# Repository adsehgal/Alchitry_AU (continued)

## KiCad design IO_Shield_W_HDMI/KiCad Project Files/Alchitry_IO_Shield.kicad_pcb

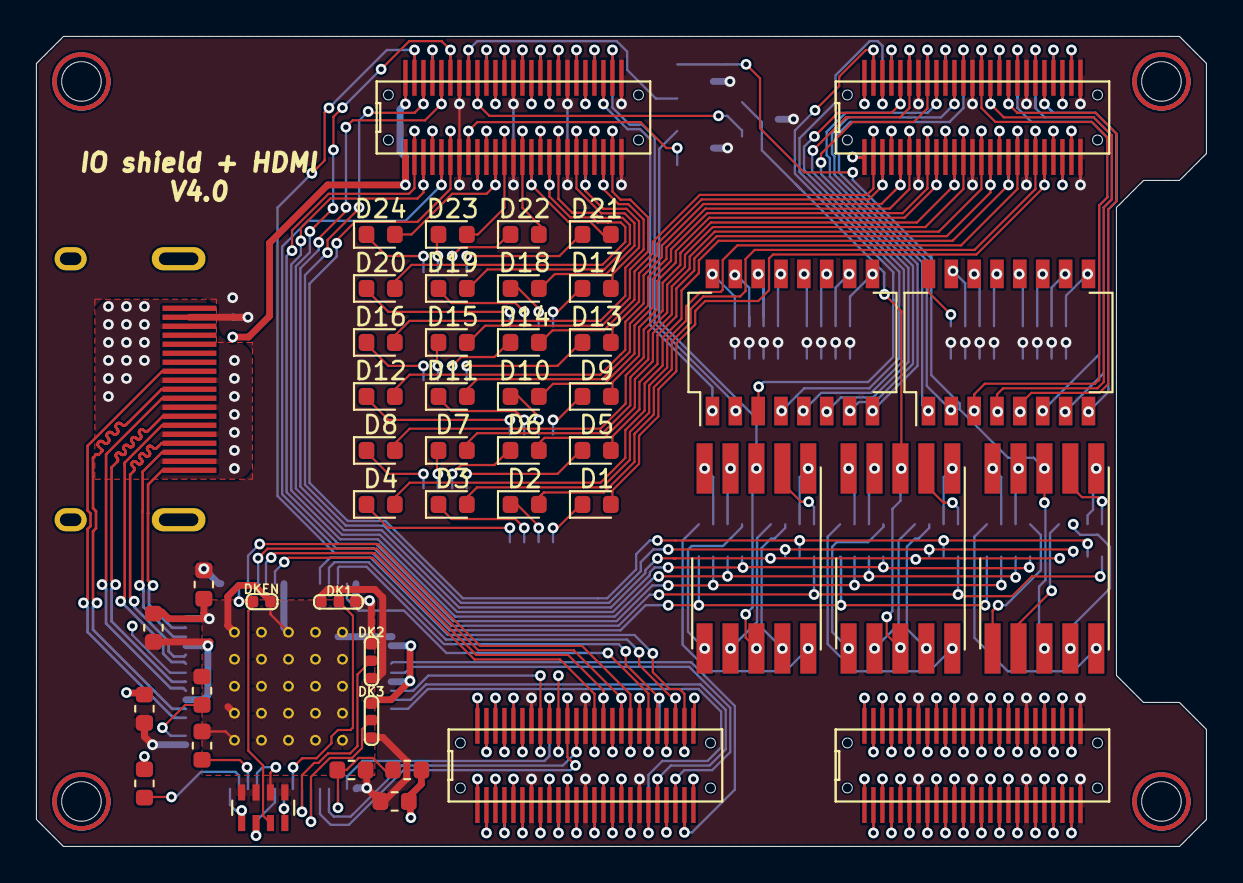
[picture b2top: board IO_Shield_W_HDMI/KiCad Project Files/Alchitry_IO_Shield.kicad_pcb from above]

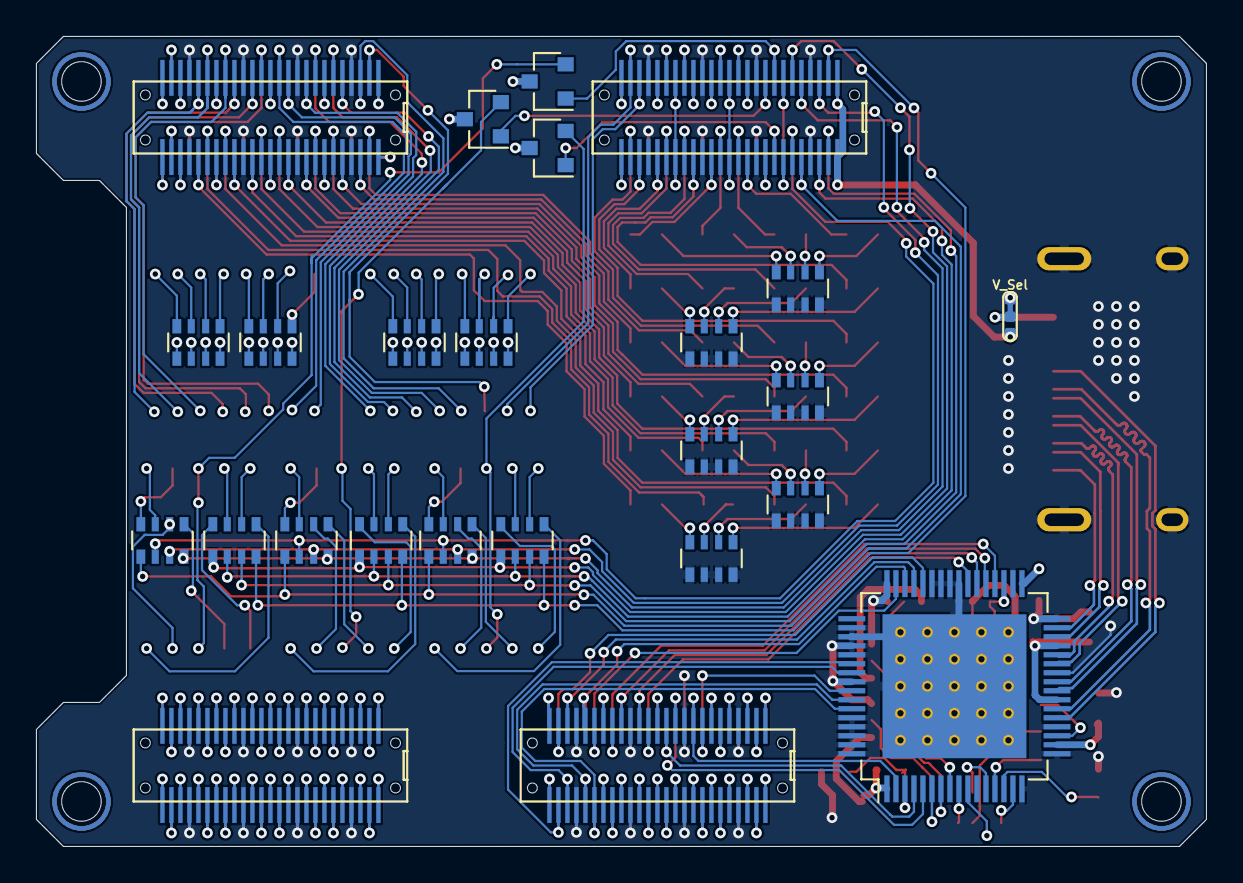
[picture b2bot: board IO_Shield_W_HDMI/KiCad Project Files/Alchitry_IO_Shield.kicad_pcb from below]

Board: 4 copper layers, 65.0 x 45.0 mm, 66 parts (21 on the bottom side), 226 nets.

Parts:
AFF1, AFF2, AFF3: LTS-6960HR; KCSC02-136
C1, C2, C3, C4: 100nF; C_0603_1608Metric
D1, D2, D3, D4, D5, D6, D7, D8, D9, D10, D11, D12, D13, D14, D15, D16, D17, D18, D19, D20, D21, D22, D23, D24: LED; LED_0603_1608Metric
J1: HDMI_A_1.4; HDMI
JP1: V_Sel; jumper_1_2_bridged
JP2: DK1; jumper_unbridged
JP3: DK2; jumper_unbridged
JP4: DK3; jumper_unbridged
JP5: DKEN; Jumper_2_Pin_Unbridged
Q1, Q2, Q3: Q_PMOS_SGD; SOT-23
R1: 510; R_0603_1608Metric
R2, R3: 10K; R_0603_1608Metric
R4: 33K; R_0603_1608Metric
R5: 91K; R_0603_1608Metric
RN1: 10K; R_Array_Concave_4x0603
RN2, RN3, RN4, RN5, RN6, RN7, RN8, RN9, RN10, RN11, RN12, RN13, RN14, RN15, RN16, RN17: R_Pack04; R_Array_Convex_4x0603
SW1, SW2: SW_DIP_x08; SW_DIP_SPSTx08_Slide_Copal_CHS-08B_W7.62mm_P1.27mm
U1: boardmezzanine_new; Alchitry_Top_Bottom
U2: TFP410; HTQFP-64-1EP_10x10mm_P0.5mm_EP8x8mm_Mask4.4x4.4mm_ThermalVi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

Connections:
+3V3: C1.1, C2.1, C3.1, C4.1, J1.18 (+5V), JP1.1 (A), JP1.2 (C), JP2.1 (A), JP3.1 (A), JP4.1 (A), Q1.3 (D), Q2.3 (D), Q3.3 (D), R1.1, R4.2, RN1.1 (R1.1), RN1.2 (R2.1), RN1.3 (R3.1), RN1.4 (R4.1), RN14.1 (R1.1), RN14.2 (R2.1), RN14.3 (R3.1), RN14.4 (R4.1), RN15.1 (R1.1), RN15.2 (R2.1), RN15.3 (R3.1), RN15.4 (R4.1), RN16.1 (R1.1), RN16.2 (R2.1), RN16.3 (R3.1), RN16.4 (R4.1), RN17.1 (R1.1), RN17.2 (R2.1), RN17.3 (R3.1), RN17.4 (R4.1), U1.AB_7, U1.AB_13, U1.AB_19, U1.AB_25, U1.AB_26, U1.AB_32, U1.AB_38, U1.AB_44, U1.AT_7 (3.3V), U1.AT_13 (3.3V), U1.AT_19 (3.3V), U1.AT_25 (3.3V), U1.AT_26 (3.3V), U1.AT_32 (3.3V), U1.AT_38 (3.3V), U1.AT_44 (3.3V), U1.BB_7, U1.BB_13, U1.BB_19, U1.BB_25, U1.BB_26, U1.BB_32, U1.BB_38, U1.BB_44, U1.BT_7 (3.3V), U1.BT_13 (3.3V), U1.BT_19 (3.3V), U1.BT_25 (3.3V), U1.BT_26 (3.3V), U1.BT_32 (3.3V), U1.BT_38 (3.3V), U1.BT_44 (3.3V), U1.CB_7, U1.CB_13, U1.CB_19, U1.CB_38, U1.CB_44, U1.CT_7 (3.3V), U1.CT_13 (3.3V), U1.CT_19 (3.3V), U1.CT_38 (3.3V), U1.CT_44 (3.3V), U1.DB_7, U1.DB_13, U1.DB_19, U1.DB_25, U1.DB_26, U1.DB_32, U1.DB_38, U1.DB_44, U1.DT_7 (3.3V), U1.DT_13 (3.3V), U1.DT_19 (3.3V), U1.DT_25 (3.3V), U1.DT_26 (3.3V), U1.DT_32 (3.3V), U1.DT_38 (3.3V), U1.DT_44 (3.3V), U2.1 (DVDD_2), U2.12 (DVDD_3), U2.18 (PVDD), U2.23 (TVDD_2), U2.29 (TVDD), U2.33 (DVDD)
+5V: JP1.3 (B), U1.AB_1, U1.AB_50, U1.AT_1 (Raw), U1.AT_50 (Raw)
/AN0: Q1.1 (G), U1.AB_43, U1.AT_43 (P9)
/AN1: Q2.1 (G), U1.AB_42, U1.AT_42 (N9)
/AN2: Q3.1 (G), U1.AB_8, U1.AT_8 (R8)
/AN3: U1.AB_9, U1.AT_9 (P8)
/B0: U1.CB_20, U1.CT_20 (N4), U2.59 (DATA4)
/B1: U1.CB_21, U1.CT_21 (M5), U2.58 (DATA5)
/B2: U1.CB_23, U1.CT_23 (L5), U2.55 (DATA6)
/B3: U1.CB_24, U1.CT_24 (P5), U2.54 (DATA7)
/BTN0: U1.BB_28, U1.BT_28 (C6)
/BTN1: U1.BB_27, U1.BT_27 (C7)
/BTN2: U1.BB_23, U1.BT_23 (A7)
/BTN3: U1.BB_24, U1.BT_24 (B7)
/BTN4: U1.CB_49, U1.CT_49 (P11)
/BTN5: U1.CB_48, U1.CT_48 (P10)
/BTN6: U1.CB_46, U1.CT_46 (N12)
/C0: RN5.1 (R1.1), RN6.1 (R1.1), RN12.1 (R1.1), U1.AB_5, U1.AT_5 (T5)
/C1: RN5.2 (R2.1), RN6.2 (R2.1), RN12.2 (R2.1), U1.AB_6, U1.AT_6 (R5)
/C2: RN5.3 (R3.1), RN6.3 (R3.1), RN12.3 (R3.1), U1.AB_48, U1.AT_48 (T9)
/C3: RN5.4 (R4.1), RN6.4 (R4.1), RN12.4 (R4.1), U1.AB_46, U1.AT_46 (R6)
/C4: RN7.1 (R1.1), RN8.1 (R1.1), RN13.1 (R1.1), U1.AB_45, U1.AT_45 (R7)
/C5: RN7.2 (R2.1), RN8.2 (R2.1), RN13.2 (R2.1), U1.AB_3, U1.AT_3 (T7)
/C6: RN7.3 (R3.1), RN8.3 (R3.1), RN13.3 (R3.1), U1.AB_2, U1.AT_2 (T8)
/CLK: U1.CB_43, U1.CT_43 (P13), U2.57 (IDCK+)
/DE: U1.CB_42, U1.CT_42 (N13), U2.2 (DE)
/DIP0: SW1.8, U1.BB_30, U1.BT_30 (D6)
/DIP1: SW1.7, U1.BB_31, U1.BT_31 (D5)
/DIP2: SW1.6, U1.BB_33, U1.BT_33 (F5)
/DIP3: SW1.5, U1.BB_34, U1.BT_34 (E5)
/DIP4: SW1.4, U1.BB_36, U1.BT_36 (G5)
/DIP5: SW1.3, U1.BB_37, U1.BT_37 (G4)
/DIP6: SW1.2, U1.BB_39, U1.BT_39 (D4)
/DIP7: SW1.1, U1.BB_40, U1.BT_40 (C4)
/DIP8: SW2.8, U1.BB_42, U1.BT_42 (E3)
/DIP9: SW2.7, U1.BB_43, U1.BT_43 (D3)
/DIP10: SW2.6, U1.BB_45, U1.BT_45 (C3)
/DIP11: SW2.5, U1.BB_46, U1.BT_46 (C2)
/DIP12: SW2.4, U1.BB_48, U1.BT_48 (C1)
/DIP13: SW2.3, U1.BB_49, U1.BT_49 (B1)
/DIP14: SW2.2, U1.AB_27, U1.AT_27 (M6)
/DIP15: SW2.1, U1.AB_28, U1.AT_28 (N6)
/DIP16: U1.AB_30, U1.AT_30 (H5)
/DIP17: U1.AB_31, U1.AT_31 (H4)
/DIP18: U1.AB_33, U1.AT_33 (J3)
/DIP19: U1.AB_34, U1.AT_34 (H3)
/DIP20: U1.AB_36, U1.AT_36 (J5)
/DIP21: U1.AB_37, U1.AT_37 (J4)
/DIP22: U1.AB_39, U1.AT_39 (K3)
/DIP23: U1.AB_40, U1.AT_40 (K2)
/DP: RN7.4 (R4.1), RN8.4 (R4.1), RN13.4 (R4.1), U1.AB_49, U1.AT_49 (T10)
/G0: U1.CB_31, U1.CT_31 (T2), U2.47 (DATA12)
/G1: U1.CB_30, U1.CT_30 (R3), U2.46 (DATA13)
/G2: U1.CB_28, U1.CT_28 (T3), U2.45 (DATA14)
/G3: U1.CB_27, U1.CT_27 (T4), U2.44 (DATA15)
/HDMI/CK+: J1.10 (CK+), U2.22 (TXC+)
/HDMI/CK-: J1.12 (CK-), U2.21 (TXC-)
/HDMI/D0+: J1.7 (D0+), U2.25 (TX0+)
/HDMI/D0-: J1.9 (D0-), U2.24 (TX0-)
/HDMI/D1+: J1.4 (D1+), U2.28 (TX1+)
/HDMI/D1-: J1.6 (D1-), U2.27 (TX1-)
/HDMI/D2+: J1.1 (D2+), U2.31 (TX2+)
/HDMI/D2-: J1.3 (D2-), U2.30 (TX2-)
/HDMI/DK1: JP2.2 (C), U2.8 (CTL1/A1/DK1)
/HDMI/DK2: JP3.2 (C), U2.7 (CTL2/A2/DK2)
/HDMI/DK3: JP4.2 (C), U2.6 (CTL3/A3/DK3)
/HDMI/ISEL: R2.1, U2.13 (ISEL/~RST)
/HS: U1.CB_39, U1.CT_39 (M2), U2.4 (HSYNC)
/LED0: D1.2 (A), U1.BB_21, U1.BT_21 (B6)
/LED1: D2.2 (A), U1.BB_20, U1.BT_20 (B5)
/LED2: D3.2 (A), U1.BB_18, U1.BT_18 (A5)
/LED3: D4.2 (A), U1.BB_17, U1.BT_17 (A4)
/LED4: D5.2 (A), U1.BB_15, U1.BT_15 (B4)
/LED5: D6.2 (A), U1.BB_14, U1.BT_14 (A3)
/LED6: D7.2 (A), U1.BB_12, U1.BT_12 (F4)
/LED7: D8.2 (A), U1.BB_11, U1.BT_11 (F3)
/LED8: D9.2 (A), U1.BB_9, U1.BT_9 (F2)
/LED9: D10.2 (A), U1.BB_8, U1.BT_8 (E1)
/LED10: D11.2 (A), U1.BB_6, U1.BT_6 (B2)
/LED11: D12.2 (A), U1.BB_5, U1.BT_5 (A2)
/LED12: D13.2 (A), U1.BB_3, U1.BT_3 (E2)
/LED13: D14.2 (A), U1.BB_2, U1.BT_2 (D1)
/LED14: D15.2 (A), U1.AB_24, U1.AT_24 (E6)
/LED15: D16.2 (A), U1.AB_23, U1.AT_23 (K5)
/LED16: D17.2 (A), U1.AB_21, U1.AT_21 (G2)
/LED17: D18.2 (A), U1.AB_20, U1.AT_20 (G1)
/LED18: D19.2 (A), U1.AB_18, U1.AT_18 (H2)
/LED19: D20.2 (A), U1.AB_17, U1.AT_17 (H1)
/LED20: D21.2 (A), U1.AB_15, U1.AT_15 (K1)
/LED21: D22.2 (A), U1.AB_14, U1.AT_14 (J1)
/LED22: D23.2 (A), U1.AB_12, U1.AT_12 (L3)
/LED23: D24.2 (A), U1.AB_11, U1.AT_11 (L2)
/R0: U1.CB_37, U1.CT_37 (P1), U2.39 (DATA20)
/R1: U1.CB_36, U1.CT_36 (N1), U2.38 (DATA21)
/R2: U1.CB_34, U1.CT_34 (R1), U2.37 (DATA22)
/R3: U1.CB_33, U1.CT_33 (R2), U2.36 (DATA23)
/VS: U1.CB_40, U1.CT_40 (M1), U2.5 (VSYNC)
GNDREF: C1.2, C2.2, C3.2, C4.2, J1.2 (D2S), J1.5 (D1S), J1.8 (D0S), J1.11 (CKS), J1.17 (GND), J1.SH, JP2.3 (B), JP3.3 (B), JP4.3 (B), JP5.1 (A), R2.2, R3.2, R5.2, RN2.1 (R1.1), RN2.2 (R2.1), RN2.3 (R3.1), RN2.4 (R4.1), RN3.1 (R1.1), RN3.2 (R2.1), RN3.3 (R3.1), RN3.4 (R4.1), RN4.1 (R1.1), RN4.2 (R2.1), RN4.3 (R3.1), RN4.4 (R4.1), RN9.1 (R1.1), RN9.2 (R2.1), RN9.3 (R3.1), RN9.4 (R4.1), RN10.1 (R1.1), RN10.2 (R2.1), RN10.3 (R3.1), RN10.4 (R4.1), RN11.1 (R1.1), RN11.2 (R2.1), RN11.3 (R3.1), RN11.4 (R4.1), U1.AB_4, U1.AB_10, U1.AB_16, U1.AB_22, U1.AB_29, U1.AB_35, U1.AB_41, U1.AB_47, U1.AT_4 (GND), U1.AT_10 (GND), U1.AT_16 (GND), U1.AT_22 (GND), U1.AT_29 (GND), U1.AT_35 (GND), U1.AT_41 (GND), U1.AT_47 (GND), U1.BB_4, U1.BB_10, U1.BB_16, U1.BB_22, U1.BB_29, U1.BB_35, U1.BB_41, U1.BB_47, U1.BT_4 (GND), U1.BT_10 (GND), U1.BT_16 (GND), U1.BT_22 (GND), U1.BT_29 (GND), U1.BT_35 (GND), U1.BT_41 (GND), U1.BT_47 (GND), U1.CB_4, U1.CB_10, U1.CB_16, U1.CB_22, U1.CB_29, U1.CB_35, U1.CB_41, U1.CB_47, U1.CT_4 (GND), U1.CT_10 (GND), U1.CT_16 (GND), U1.CT_22 (GND), U1.CT_29 (GND), U1.CT_35 (GND), U1.CT_41 (GND), U1.CT_47 (GND), U1.DB_4, U1.DB_10, U1.DB_16, U1.DB_22, U1.DB_29, U1.DB_35, U1.DB_41, U1.DB_47, U1.DT_4 (GND), U1.DT_10 (GND), U1.DT_16 (GND), U1.DT_22 (GND), U1.DT_29 (GND), U1.DT_35 (GND), U1.DT_41 (GND), U1.DT_47 (GND), U2.16 (DGND_3), U2.17 (PGND), U2.20 (TGND_2), U2.26 (TGND_3), U2.32 (TGND), U2.34 (RESERVED), U2.40 (DATA19), U2.41 (DATA18), U2.42 (DATA17), U2.43 (DATA16), U2.48 (DGND_2), U2.50 (DATA11), U2.51 (DATA10), U2.52 (DATA9), U2.53 (DATA8), U2.56 (IDCK-), U2.60 (DATA3), U2.61 (DATA2), U2.62 (DATA1), U2.63 (DATA0), U2.64 (DGND), U2.65 (PAD)
unnamed: AFF1.1 (e), RN7.8 (R1.2)
unnamed: AFF1.2 (d), RN5.5 (R4.2)
unnamed: AFF1.3 (C.A.), AFF1.8 (C.A.), Q1.2 (S)
unnamed: AFF1.4 (c), RN5.6 (R3.2)
unnamed: AFF1.5 (DP), RN7.5 (R4.2)
unnamed: AFF1.6 (b), RN5.7 (R2.2)
unnamed: AFF1.7 (a), RN5.8 (R1.2)
unnamed: AFF1.9 (f), RN7.7 (R2.2)
unnamed: AFF1.10 (g), RN7.6 (R3.2)
unnamed: AFF2.1 (e), RN8.8 (R1.2)
unnamed: AFF2.2 (d), RN6.5 (R4.2)
unnamed: AFF2.3 (C.A.), AFF2.8 (C.A.), Q2.2 (S)
unnamed: AFF2.4 (c), RN6.6 (R3.2)
unnamed: AFF2.5 (DP), RN8.5 (R4.2)
unnamed: AFF2.6 (b), RN6.7 (R2.2)
unnamed: AFF2.7 (a), RN6.8 (R1.2)
unnamed: AFF2.9 (f), RN8.7 (R2.2)
unnamed: AFF2.10 (g), RN8.6 (R3.2)
unnamed: AFF3.1 (e), RN13.8 (R1.2)
unnamed: AFF3.2 (d), RN12.5 (R4.2)
unnamed: AFF3.3 (C.A.), AFF3.8 (C.A.), Q3.2 (S)
unnamed: AFF3.4 (c), RN12.6 (R3.2)
unnamed: AFF3.5 (DP), RN13.5 (R4.2)
unnamed: AFF3.6 (b), RN12.7 (R2.2)
unnamed: AFF3.7 (a), RN12.8 (R1.2)
unnamed: AFF3.9 (f), RN13.7 (R2.2)
unnamed: AFF3.10 (g), RN13.6 (R3.2)
unnamed: D1.1 (K), RN2.8 (R1.2)
unnamed: D2.1 (K), RN2.7 (R2.2)
unnamed: D3.1 (K), RN2.6 (R3.2)
unnamed: D4.1 (K), RN2.5 (R4.2)
unnamed: D5.1 (K), RN3.8 (R1.2)
unnamed: D6.1 (K), RN3.7 (R2.2)
unnamed: D7.1 (K), RN3.6 (R3.2)
unnamed: D8.1 (K), RN3.5 (R4.2)
unnamed: D9.1 (K), RN4.8 (R1.2)
unnamed: D10.1 (K), RN4.7 (R2.2)
unnamed: D11.1 (K), RN4.6 (R3.2)
unnamed: D12.1 (K), RN4.5 (R4.2)
unnamed: D13.1 (K), RN9.8 (R1.2)
unnamed: D14.1 (K), RN9.7 (R2.2)
unnamed: D15.1 (K), RN9.6 (R3.2)
unnamed: D16.1 (K), RN9.5 (R4.2)
unnamed: D17.1 (K), RN10.8 (R1.2)
unnamed: D18.1 (K), RN10.7 (R2.2)
unnamed: D19.1 (K), RN10.6 (R3.2)
unnamed: D20.1 (K), RN10.5 (R4.2)
unnamed: D21.1 (K), RN11.8 (R1.2)
unnamed: D22.1 (K), RN11.7 (R2.2)
unnamed: D23.1 (K), RN11.6 (R3.2)
unnamed: D24.1 (K), RN11.5 (R4.2)
unnamed: JP5.2 (B), RN1.7 (R2.2), U2.35 (DKEN)
unnamed: R1.2, U2.19 (TFADJ)
unnamed: R3.1, U2.14 (DSEL/SDA)
unnamed: R4.1, R5.1, U2.3 (VREF)
unnamed: RN1.5 (R4.2), U2.15 (BSEL/SCL)
unnamed: RN1.6 (R3.2), U2.10 (~PD)
unnamed: RN1.8 (R1.2), U2.9 (EDGE/HTPLG)
unnamed: RN14.5 (R4.2), SW1.12
unnamed: RN14.6 (R3.2), SW1.11
unnamed: RN14.7 (R2.2), SW1.10
unnamed: RN14.8 (R1.2), SW1.9
unnamed: RN15.5 (R4.2), SW1.16
unnamed: RN15.6 (R3.2), SW1.15
unnamed: RN15.7 (R2.2), SW1.14
unnamed: RN15.8 (R1.2), SW1.13
unnamed: RN16.5 (R4.2), SW2.12
unnamed: RN16.6 (R3.2), SW2.11
unnamed: RN16.7 (R2.2), SW2.10
unnamed: RN16.8 (R1.2), SW2.9
unnamed: RN17.5 (R4.2), SW2.16
unnamed: RN17.6 (R3.2), SW2.15
unnamed: RN17.7 (R2.2), SW2.14
unnamed: RN17.8 (R1.2), SW2.13
unnamed: U1.BB_1, U1.BT_1 (Raw)
unnamed: U1.BB_50, U1.BT_50 (Raw)
unnamed: U1.CB_1, U1.CT_1 (Raw)
unnamed: U1.CB_2, U1.CT_2 (T13)
unnamed: U1.CB_3, U1.CT_3 (R13)
unnamed: U1.CB_5, U1.CT_5 (T12)
unnamed: U1.CB_6, U1.CT_6 (R12)
unnamed: U1.CB_8, U1.CT_8 (R11)
unnamed: U1.CB_9, U1.CT_9 (R10)
unnamed: U1.CB_11, U1.CT_11 (N2)
unnamed: U1.CB_12, U1.CT_12 (N3)
unnamed: U1.CB_14, U1.CT_14 (P3)
unnamed: U1.CB_15, U1.CT_15 (P4)
unnamed: U1.CB_17, U1.CT_17 (M4)
unnamed: U1.CB_18, U1.CT_18 (L4)
unnamed: U1.CB_25, U1.CT_25 (3.3V)
unnamed: U1.CB_26, U1.CT_26 (3.3V)
unnamed: U1.CB_32, U1.CT_32 (3.3V)
unnamed: U1.CB_45, U1.CT_45 (N11)
unnamed: U1.CB_50, U1.CT_50 (Raw)
unnamed: U1.DB_1, U1.DT_1 (Raw)
unnamed: U1.DB_2, U1.DT_2 (LED2)
unnamed: U1.DB_3, U1.DT_3 (LED3)
unnamed: U1.DB_5, U1.DT_5 (LED6)
unnamed: U1.DB_6, U1.DT_6 (LED7)
unnamed: U1.DB_8, U1.DT_8 (R16)
unnamed: U1.DB_9, U1.DT_9 (R15)
unnamed: U1.DB_11, U1.DT_11 (P14)
unnamed: U1.DB_12, U1.DT_12 (M15)
unnamed: U1.DB_14, U1.DT_14 (TX)
unnamed: U1.DB_15, U1.DT_15 (RX)
unnamed: U1.DB_17, U1.DT_17
unnamed: U1.DB_18, U1.DT_18
unnamed: U1.DB_20, U1.DT_20
unnamed: U1.DB_21, U1.DT_21
unnamed: U1.DB_23, U1.DT_23
unnamed: U1.DB_24, U1.DT_24
unnamed: U1.DB_27, U1.DT_27
unnamed: U1.DB_28, U1.DT_28
unnamed: U1.DB_30, U1.DT_30
unnamed: U1.DB_31, U1.DT_31
unnamed: U1.DB_33, U1.DT_33
unnamed: U1.DB_34, U1.DT_34
unnamed: U1.DB_36, U1.DT_36
unnamed: U1.DB_37, U1.DT_37
unnamed: U1.DB_39, U1.DT_39 (RESET)
unnamed: U1.DB_40, U1.DT_40 (100MHz)
unnamed: U1.DB_42, U1.DT_42 (T14)
unnamed: U1.DB_43, U1.DT_43 (T15)
unnamed: U1.DB_45, U1.DT_45 (LED5)
unnamed: U1.DB_46, U1.DT_46 (LED4)
unnamed: U1.DB_48, U1.DT_48 (LED1)
unnamed: U1.DB_49, U1.DT_49 (LED0)
unnamed: U1.DB_50, U1.DT_50 (Raw)

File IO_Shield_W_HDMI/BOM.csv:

Comment,Designator,Footprint,LCSC
"LTS-6960HR","AFF1,AFF2,AFF3","Display_7Segment:KCSC02-136",""
"100nF","C1,C2,C3,C4","Capacitor_SMD:C_0603_1608Metric",""
"LED","D1,D2,D3,D4,D5,D6,D7,D8,D9,D10,D11,D12,D13,D14,D15,D16,D17,D18,D19,D20,D21,D22,D23,D24","LED_SMD:LED_0603_1608Metric",""
"HDMI_A_1.4","J1","Custom_Parts:HDMI",""
"V_Sel","JP1","Custom_Parts:jumper_1_2_bridged",""
"DK1","JP2","Custom_Parts:jumper_unbridged",""
"DK2","JP3","Custom_Parts:jumper_unbridged",""
"DK3","JP4","Custom_Parts:jumper_unbridged",""
"DKEN","JP5","Custom_Parts:Jumper_2_Pin_Unbridged",""
"Q_PMOS_SGD","Q1,Q2,Q3","Package_TO_SOT_SMD:SOT-23",""
"510R","R1","Resistor_SMD:R_0603_1608Metric",""
"10K","R2,R3","Resistor_SMD:R_0603_1608Metric",""
"33K","R4","Resistor_SMD:R_0603_1608Metric",""
"91K","R5","Resistor_SMD:R_0603_1608Metric",""
"10K","RN1","Resistor_SMD:R_Array_Concave_4x0603",""
"R_Pack04","RN2,RN3,RN4,RN5,RN6,RN7,RN8,RN9,RN10,RN11,RN12,RN13,RN14,RN15,RN16,RN17","Resistor_SMD:R_Array_Convex_4x0603",""
"SW_DIP_x08","SW1,SW2","Button_Switch_SMD:SW_DIP_SPSTx08_Slide_Copal_CHS-08B_W7.62mm_P1.27mm",""
"boardmezzanine_new","U1","Custom_Parts:Alchitry_Top_Bottom",""
"TFP410","U2","Package_QFP:HTQFP-64-1EP_10x10mm_P0.5mm_EP8x8mm_Mask4.4x4.4mm_ThermalVias",""

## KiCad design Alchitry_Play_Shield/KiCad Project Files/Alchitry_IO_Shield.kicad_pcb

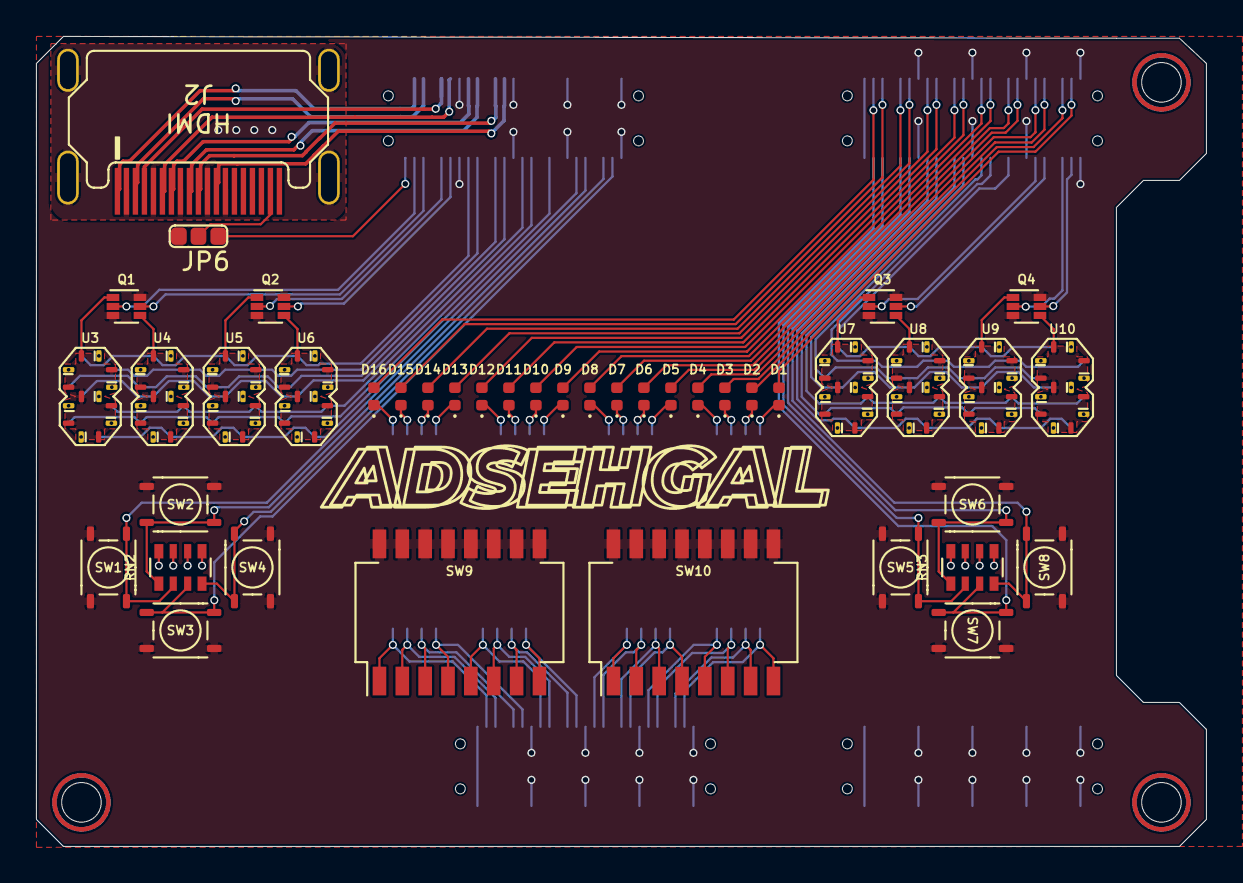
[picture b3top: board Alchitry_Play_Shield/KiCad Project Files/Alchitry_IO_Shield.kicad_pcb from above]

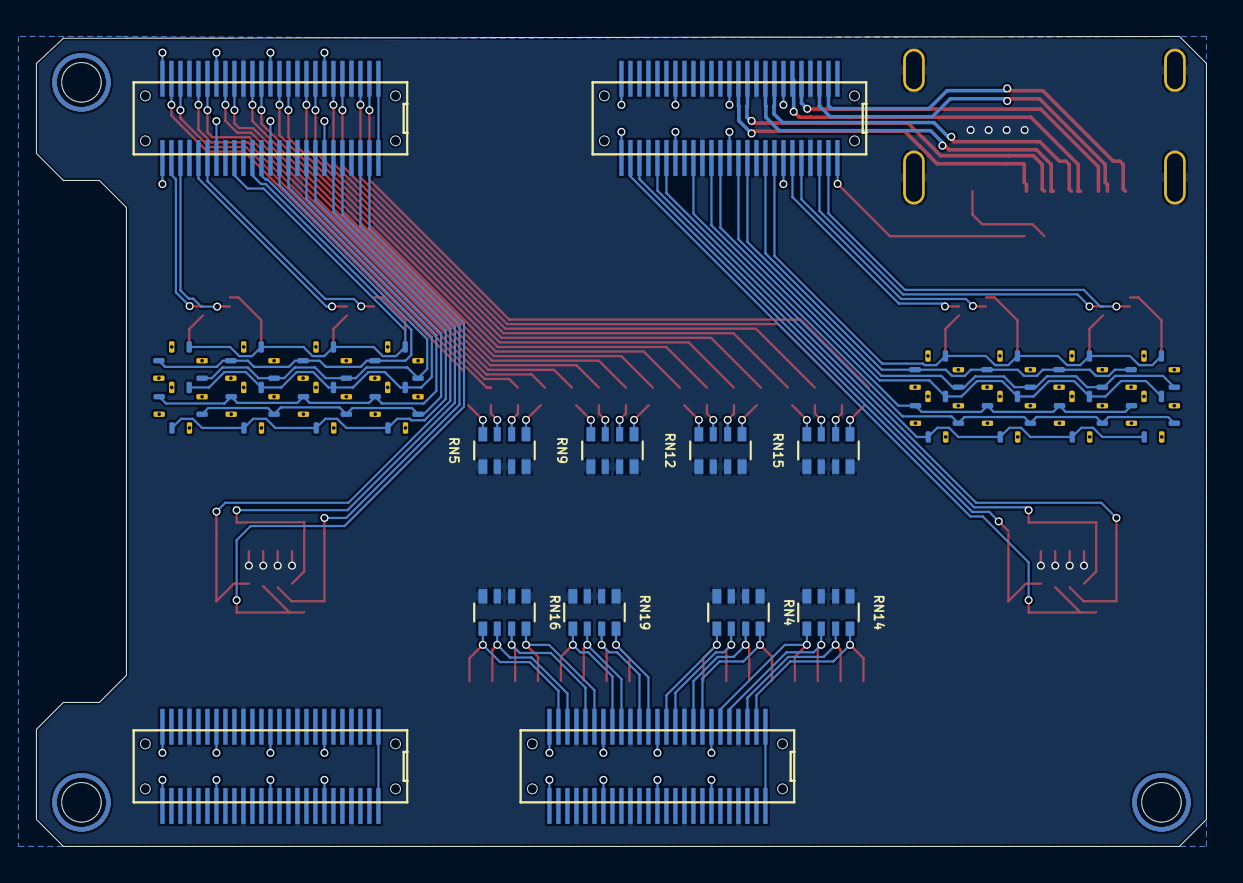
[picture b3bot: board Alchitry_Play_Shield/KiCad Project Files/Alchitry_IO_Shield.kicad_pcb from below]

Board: 2 copper layers, 65.0 x 45.0 mm, 51 parts (8 on the bottom side), 98 nets.

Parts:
D1, D2, D3, D4, D5, D6, D7, D8, D9, D10, D11, D12, D13, D14, D15, D16: LED; LED_0402_1005Metric
J2: C168714_HDMI_Atype
JP6: V_Sel; jumper_unbridged
Q1, Q2, Q3, Q4: NTZD3152P; SOT-563
RN2, RN3, RN4, RN5, RN9, RN12, RN14, RN15, RN16, RN19: R_Pack04; R_Array_Convex_4x0603
SW1, SW5: SW3; Korean Hroparts Elec K2-1177SR
SW2, SW6: SW1; Korean Hroparts Elec K2-1177SR
SW3, SW7: SW2; Korean Hroparts Elec K2-1177SR
SW4, SW8: SW4; Korean Hroparts Elec K2-1177SR
SW9, SW10: SW_DIP_x08; SW_DIP_SPSTx08_Slide_Copal_CHS-08B_W7.62mm_P1.27mm
U1: Alchitry_Single; Alchitry_Bottom
U3, U4, U5, U6, U7, U8, U9, U10: 0402_7Seg_CA; 0402_7Seg_CA_W_Res

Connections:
+3V3: JP6.1 (A), Q1.3 (D), Q1.6 (D), Q2.3 (D), Q2.6 (D), Q3.3 (D), Q3.6 (D), Q4.3 (D), Q4.6 (D), SW1.2, SW2.2, SW3.2, SW4.2, SW5.2, SW6.2, SW7.2, SW8.2, SW9.9, SW9.10, SW9.11, SW9.12, SW9.13, SW9.14, SW9.15, SW9.16, SW10.9, SW10.10, SW10.11, SW10.12, SW10.13, SW10.14, SW10.15, SW10.16, U1.A_7 (3.3V), U1.A_13 (3.3V), U1.A_19 (3.3V), U1.A_25 (3.3V), U1.A_26 (3.3V), U1.A_32 (3.3V), U1.A_38 (3.3V), U1.A_44 (3.3V), U1.B_7 (3.3V), U1.B_13 (3.3V), U1.B_19 (3.3V), U1.B_25 (3.3V), U1.B_26 (3.3V), U1.B_32 (3.3V), U1.B_38 (3.3V), U1.B_44 (3.3V), U1.C_7 (3.3V), U1.C_13 (3.3V), U1.C_19 (3.3V), U1.C_25 (3.3V), U1.C_26 (3.3V), U1.C_32 (3.3V), U1.C_38 (3.3V), U1.C_44 (3.3V), U1.D_7 (3.3V), U1.D_13 (3.3V), U1.D_19 (3.3V), U1.D_25 (3.3V), U1.D_26 (3.3V), U1.D_32 (3.3V), U1.D_38 (3.3V), U1.D_44 (3.3V)
+5V: JP6.3 (B), U1.A_1 (Raw), U1.A_50 (Raw), U1.B_1 (Raw), U1.B_50 (Raw), U1.C_1 (Raw), U1.C_50 (Raw), U1.D_1 (Raw), U1.D_50 (Raw)
/ANL1: Q1.2 (G), U1.A_2 (T8)
/ANL2: Q1.5 (G), U1.A_3 (T7)
/ANL3: Q2.2 (G), U1.A_5 (T5)
/ANL4: Q2.5 (G), U1.A_6 (R5)
/ANR1: Q3.2 (G), U1.B_20 (B5)
/ANR2: Q3.5 (G), U1.B_21 (B6)
/ANR3: Q4.2 (G), U1.B_23 (A7)
/ANR4: Q4.5 (G), U1.B_24 (B7)
/CK+: J2.10 (CK+), U1.A_40 (K2)
/CK-: J2.12 (CK-), U1.A_39 (K3)
/CL1: U1.A_9 (P8), U3.1 (a), U4.1 (a), U5.1 (a), U6.1 (a)
/CL2: U1.A_14 (J1), U3.2 (b), U4.2 (b), U5.2 (b), U6.2 (b)
/CL3: U1.A_17 (H1), U3.3 (c), U4.3 (c), U5.3 (c), U6.3 (c)
/CL4: U1.A_15 (K1), U3.4 (d), U4.4 (d), U5.4 (d), U6.4 (d)
/CL5: U1.A_11 (L2), U3.5 (e), U4.5 (e), U5.5 (e), U6.5 (e)
/CL6: U1.A_8 (R8), U3.6 (f), U4.6 (f), U5.6 (f), U6.6 (f)
/CL7: U1.A_12 (L3), U3.7 (g), U4.7 (g), U5.7 (g), U6.7 (g)
/CR1: U1.B_15 (B4), U7.1 (a), U8.1 (a), U9.1 (a), U10.1 (a)
/CR2: U1.B_11 (F3), U7.2 (b), U8.2 (b), U9.2 (b), U10.2 (b)
/CR3: U1.B_8 (E1), U7.3 (c), U8.3 (c), U9.3 (c), U10.3 (c)
/CR4: U1.B_9 (F2), U7.4 (d), U8.4 (d), U9.4 (d), U10.4 (d)
/CR5: U1.B_14 (A3), U7.5 (e), U8.5 (e), U9.5 (e), U10.5 (e)
/CR6: U1.B_17 (A4), U7.6 (f), U8.6 (f), U9.6 (f), U10.6 (f)
/CR7: U1.B_12 (F4), U7.7 (g), U8.7 (g), U9.7 (g), U10.7 (g)
/D0+: J2.7 (D0+), U1.A_43 (P9)
/D0-: J2.9 (D0-), U1.A_42 (N9)
/D1+: J2.4 (D1+), U1.A_46 (R6)
/D1-: J2.6 (D1-), U1.A_45 (R7)
/D2+: J2.1 (D2+), U1.A_49 (T10)
/D2-: J2.3 (D2-), U1.A_48 (T9)
/DIP1: RN16.5 (R4.2), SW10.8, U1.C_27 (T4)
/DIP2: RN16.6 (R3.2), SW10.7, U1.C_28 (T3)
/DIP3: RN16.7 (R2.2), SW10.6, U1.C_30 (R3)
/DIP4: RN16.8 (R1.2), SW10.5, U1.C_31 (T2)
/DIP5: RN19.5 (R4.2), SW10.4, U1.C_33 (R2)
/DIP6: RN19.6 (R3.2), SW10.3, U1.C_34 (R1)
/DIP7: RN19.7 (R2.2), SW10.2, U1.C_36 (N1)
/DIP8: RN19.8 (R1.2), SW10.1, U1.C_37 (P1)
/DIP9: RN4.5 (R4.2), SW9.8, U1.C_39 (M2)
/DIP10: RN4.6 (R3.2), SW9.7, U1.C_40 (M1)
/DIP11: RN4.7 (R2.2), SW9.6, U1.C_42 (N13)
/DIP12: RN4.8 (R1.2), SW9.5, U1.C_43 (P13)
/DIP13: RN14.5 (R4.2), SW9.4, U1.C_45 (N11)
/DIP14: RN14.6 (R3.2), SW9.3, U1.C_46 (N12)
/DIP15: RN14.7 (R2.2), SW9.2, U1.C_48 (P10)
/DIP16: RN14.8 (R1.2), SW9.1, U1.C_49 (P11)
/LED1: D1.2 (A), U1.B_27 (C7)
/LED2: D2.2 (A), U1.B_28 (C6)
/LED3: D3.2 (A), U1.B_30 (D6)
/LED4: D4.2 (A), U1.B_31 (D5)
/LED5: D5.2 (A), U1.B_33 (F5)
/LED6: D6.2 (A), U1.B_34 (E5)
/LED7: D7.2 (A), U1.B_36 (G5)
/LED8: D8.2 (A), U1.B_37 (G4)
/LED9: D9.2 (A), U1.B_39 (D4)
/LED10: D10.2 (A), U1.B_40 (C4)
/LED11: D11.2 (A), U1.B_42 (E3)
/LED12: D12.2 (A), U1.B_43 (D3)
/LED13: D13.2 (A), U1.B_45 (C3)
/LED14: D14.2 (A), U1.B_46 (C2)
/LED15: D15.2 (A), U1.B_48 (C1)
/LED16: D16.2 (A), U1.B_49 (B1)
/SWL1: RN2.1 (R1.1), SW2.1, U1.A_21 (G2)
/SWL2: RN2.3 (R3.1), SW3.1, U1.A_24 (E6)
/SWL3: RN2.2 (R2.1), SW1.1, U1.A_20 (G1)
/SWL4: RN2.4 (R4.1), SW4.1, U1.A_23 (K5)
/SWR1: RN3.1 (R1.1), SW6.1, U1.B_5 (A2)
/SWR2: RN3.3 (R3.1), SW7.1, U1.B_2 (D1)
/SWR3: RN3.2 (R2.1), SW5.1, U1.B_3 (E2)
/SWR4: RN3.4 (R4.1), SW8.1, U1.B_6 (B2)
GNDREF: J2.2 (D2S), J2.5 (D1S), J2.8 (D0S), J2.11 (CKS), J2.13 (CEC), J2.17 (GND), J2.SH, RN2.5 (R4.2), RN2.6 (R3.2), RN2.7 (R2.2), RN2.8 (R1.2), RN3.5 (R4.2), RN3.6 (R3.2), RN3.7 (R2.2), RN3.8 (R1.2), RN4.1 (R1.1), RN4.2 (R2.1), RN4.3 (R3.1), RN4.4 (R4.1), RN5.1 (R1.1), RN5.2 (R2.1), RN5.3 (R3.1), RN5.4 (R4.1), RN9.1 (R1.1), RN9.2 (R2.1), RN9.3 (R3.1), RN9.4 (R4.1), RN12.1 (R1.1), RN12.2 (R2.1), RN12.3 (R3.1), RN12.4 (R4.1), RN14.1 (R1.1), RN14.2 (R2.1), RN14.3 (R3.1), RN14.4 (R4.1), RN15.1 (R1.1), RN15.2 (R2.1), RN15.3 (R3.1), RN15.4 (R4.1), RN16.1 (R1.1), RN16.2 (R2.1), RN16.3 (R3.1), RN16.4 (R4.1), RN19.1 (R1.1), RN19.2 (R2.1), RN19.3 (R3.1), RN19.4 (R4.1), U1.A_4 (GND), U1.A_10 (GND), U1.A_16 (GND), U1.A_22 (GND), U1.A_29 (GND), U1.A_35 (GND), U1.A_41 (GND), U1.A_47 (GND), U1.B_4 (GND), U1.B_10 (GND), U1.B_16 (GND), U1.B_22 (GND), U1.B_29 (GND), U1.B_35 (GND), U1.B_41 (GND), U1.B_47 (GND), U1.C_4 (GND), U1.C_10 (GND), U1.C_16 (GND), U1.C_22 (GND), U1.C_29 (GND), U1.C_35 (GND), U1.C_41 (GND), U1.C_47 (GND), U1.D_4 (GND), U1.D_10 (GND), U1.D_16 (GND), U1.D_22 (GND), U1.D_29 (GND), U1.D_35 (GND), U1.D_41 (GND), U1.D_47 (GND)
unnamed: D1.1 (K), RN5.8 (R1.2)
unnamed: D2.1 (K), RN5.7 (R2.2)
unnamed: D3.1 (K), RN5.6 (R3.2)
unnamed: D4.1 (K), RN5.5 (R4.2)
unnamed: D5.1 (K), RN9.8 (R1.2)
unnamed: D6.1 (K), RN9.7 (R2.2)
unnamed: D7.1 (K), RN9.6 (R3.2)
unnamed: D8.1 (K), RN9.5 (R4.2)
unnamed: D9.1 (K), RN12.8 (R1.2)
unnamed: D10.1 (K), RN12.7 (R2.2)
unnamed: D11.1 (K), RN12.6 (R3.2)
unnamed: D12.1 (K), RN12.5 (R4.2)
unnamed: D13.1 (K), RN15.8 (R1.2)
unnamed: D14.1 (K), RN15.7 (R2.2)
unnamed: D15.1 (K), RN15.6 (R3.2)
unnamed: D16.1 (K), RN15.5 (R4.2)
unnamed: J2.18 (+5V), JP6.2 (C)
unnamed: Q1.1 (S), U3.8 (C.A.)
unnamed: Q1.4 (S), U4.8 (C.A.)
unnamed: Q2.1 (S), U5.8 (C.A.)
unnamed: Q2.4 (S), U6.8 (C.A.)
unnamed: Q3.1 (S), U7.8 (C.A.)
unnamed: Q3.4 (S), U8.8 (C.A.)
unnamed: Q4.1 (S), U9.8 (C.A.)
unnamed: Q4.4 (S), U10.8 (C.A.)
